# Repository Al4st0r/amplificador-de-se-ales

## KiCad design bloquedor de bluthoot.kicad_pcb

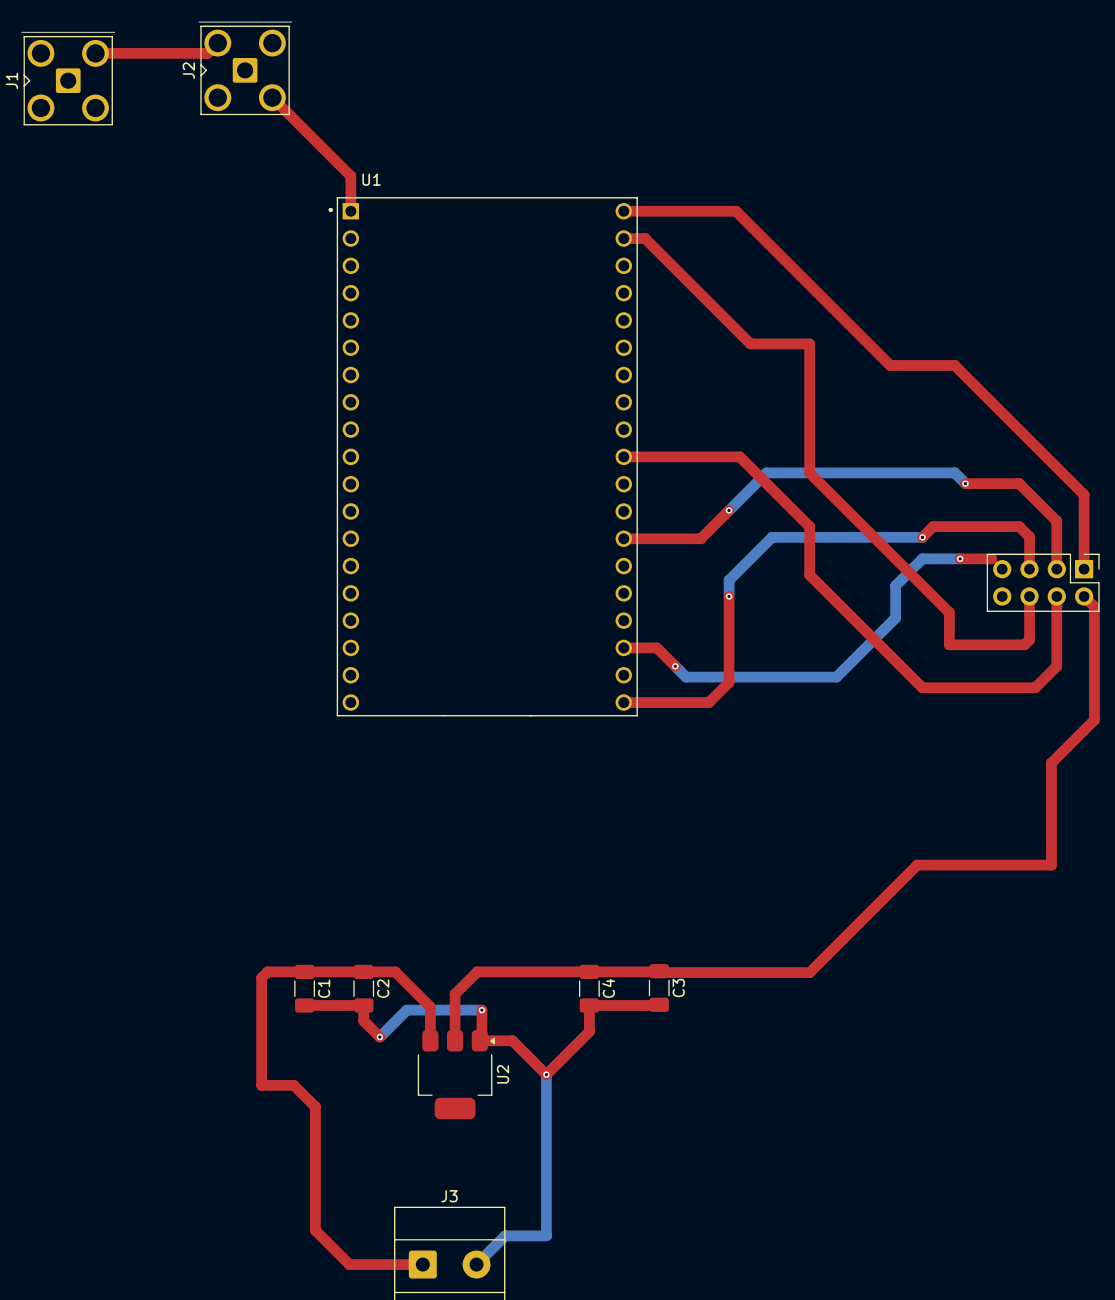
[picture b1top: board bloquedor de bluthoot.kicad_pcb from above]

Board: 2 copper layers, 10 parts (0 on the bottom side), 8 nets.

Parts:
C1, C2, C3, C4: C; C_1206_3216Metric_Pad1.33x1.80mm_HandSolder
J1, J2: Conn_Coaxial; SMA_Amphenol_901-143_Horizontal
J3: Screw_Terminal_01x02; TerminalBlock_Phoenix_MKDS-1,5-2_1x02_P5.00mm_Horizontal
U1: ESP32-WROOM-32U; MODULE_ESP32-DEVKITC-32U
U2: AMS1117-3.3; SOT-223-3_TabPin2
U4: NRF24L01_Breakout; PinHeader_2x04_P2.54mm_Vertical

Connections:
GND1: C1.2, C2.2, C3.2, C4.2, J1.2 (Ext_2), J2.2 (Ext_2), J3.2, U1.1 (GND), U1.15 (GND), U1.38 (GND), U2.1 (GND), U4.1 (GND)
unnamed: C1.1, C2.1, J3.1, U2.3 (VI)
unnamed: U1.26 (IO4), U4.3 (CE)
unnamed: U1.29 (IO5), U4.4 (~CSN)
unnamed: U1.37 (IO23), U4.6 (MOSI)
unnamed: U1.20 (SCK/CLK), U4.5 (SCK)
unnamed: U1.22 (SDI/SD1), U4.7 (MISO)
unnamed: C3.1, C4.1, U1.2 (VDD), U2.2 (VO), U4.2 (VCC)
